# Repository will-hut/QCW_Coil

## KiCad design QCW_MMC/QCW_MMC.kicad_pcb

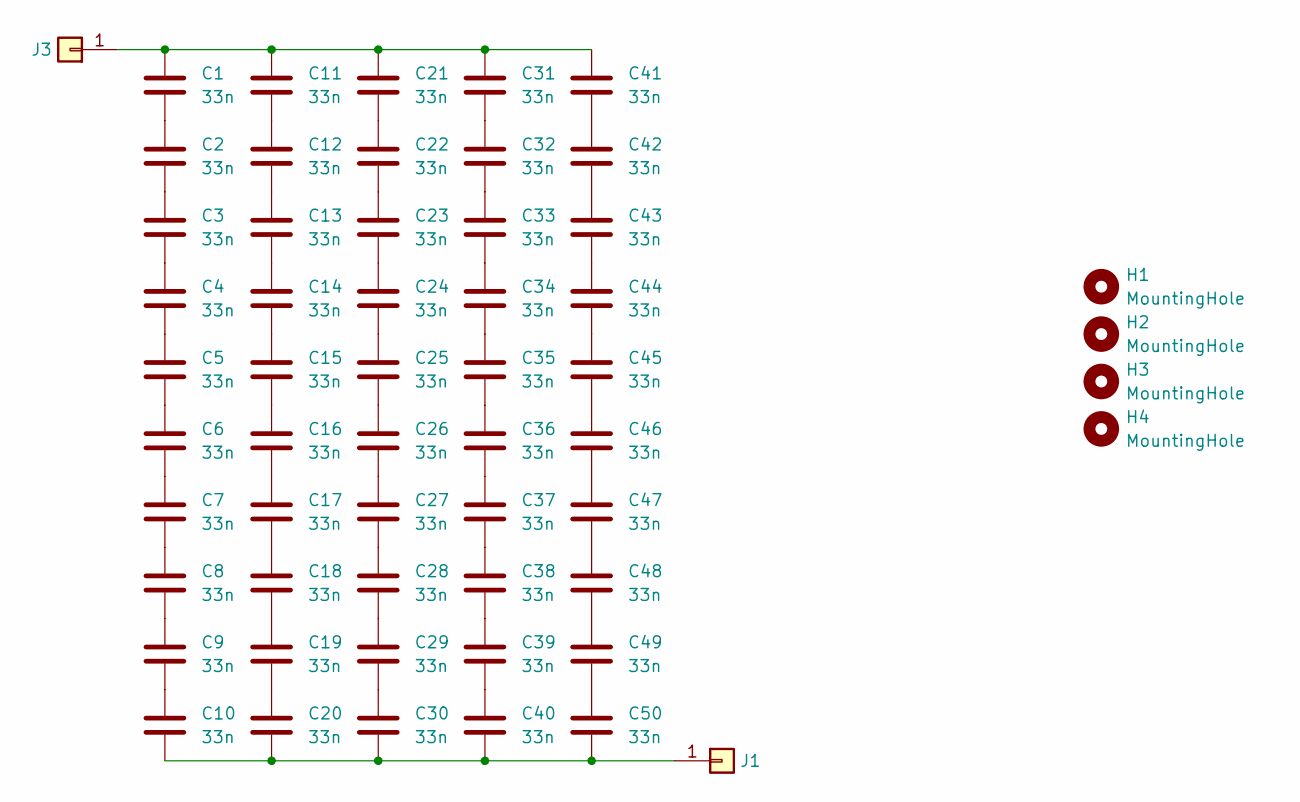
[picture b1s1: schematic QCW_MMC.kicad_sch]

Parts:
C1, C2, C3, C4, C5, C6, C7, C8, C9, C10, C11, C12, C13, C14, C15, C16, C17, C18, C19, C20, C21, C22, C23, C24, C25, C26, C27, C28, C29, C30, C31, C32, C33, C34, C35, C36, C37, C38, C39, C40, C41, C42, C43, C44, C45, C46, C47, C48, C49, C50: 33n; C_Rect_L18.0mm_W5.0mm_P15.00mm_FKS3_FKP3
H1, H2, H3, H4: MountingHole; MountingHole_5.3mm_M5
J1, J3: Conn_01x01; M6 Lug

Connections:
unnamed: C1.2, C2.1
unnamed: C2.2, C3.1
unnamed: C3.2, C4.1
unnamed: C4.2, C5.1
unnamed: C5.2, C6.1
unnamed: C6.2, C7.1
unnamed: C7.2, C8.1
unnamed: C8.2, C9.1
unnamed: C9.2, C10.1
unnamed: C11.2, C12.1
unnamed: C12.2, C13.1
unnamed: C13.2, C14.1
unnamed: C14.2, C15.1
unnamed: C15.2, C16.1
unnamed: C16.2, C17.1
unnamed: C17.2, C18.1
unnamed: C18.2, C19.1
unnamed: C19.2, C20.1
unnamed: C21.2, C22.1
unnamed: C22.2, C23.1
unnamed: C23.2, C24.1
unnamed: C24.2, C25.1
unnamed: C25.2, C26.1
unnamed: C26.2, C27.1
unnamed: C27.2, C28.1
unnamed: C28.2, C29.1
unnamed: C29.2, C30.1
unnamed: C31.2, C32.1
unnamed: C32.2, C33.1
unnamed: C33.2, C34.1
unnamed: C34.2, C35.1
unnamed: C35.2, C36.1
unnamed: C36.2, C37.1
unnamed: C37.2, C38.1
unnamed: C38.2, C39.1
unnamed: C39.2, C40.1
unnamed: C41.2, C42.1
unnamed: C42.2, C43.1
unnamed: C43.2, C44.1
unnamed: C44.2, C45.1
unnamed: C45.2, C46.1
unnamed: C46.2, C47.1
unnamed: C47.2, C48.1
unnamed: C48.2, C49.1
unnamed: C49.2, C50.1
unnamed: C10.2, C20.2, C30.2, C40.2, C50.2, J1.1
unnamed: C1.1, C11.1, C21.1, C31.1, C41.1, J3.1

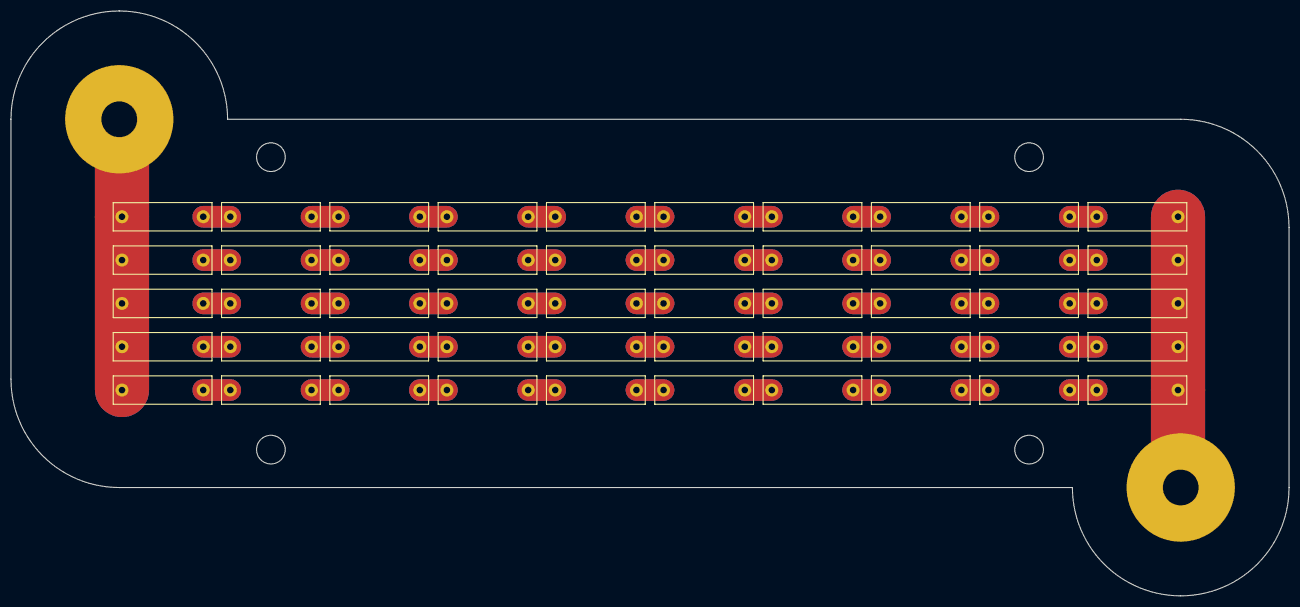
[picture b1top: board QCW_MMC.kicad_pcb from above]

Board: 2 copper layers, 236.0 x 108.0 mm, 56 parts (0 on the bottom side), 47 nets.

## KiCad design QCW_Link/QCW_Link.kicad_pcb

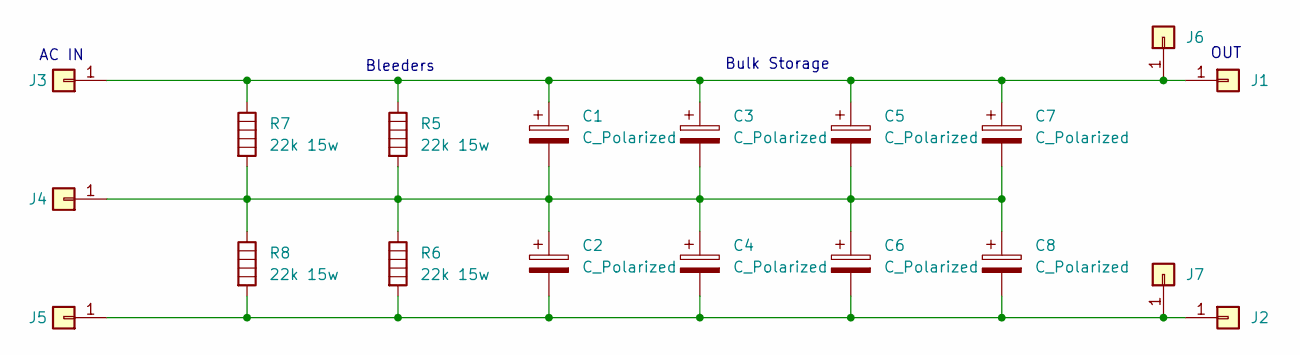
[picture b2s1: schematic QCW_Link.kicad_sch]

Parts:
C1, C2, C3, C4, C5, C6, C7, C8: C_Polarized; EPCOS B43456-S5129-M2
J1, J2, J3, J4, J5: Conn_01x01; M6 Lug
J6, J7: Conn_01x01; SolderWirePad_1x01_SMD_1.5x3mm
R5, R6, R7, R8: 22k 15w; R_Axial_Power_L48.0mm_W12.5mm_P55.88mm

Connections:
unnamed: C1.1, C3.1, C5.1, C7.1, J1.1, J3.1, J6.1, R5.1, R7.1
unnamed: C2.2, C4.2, C6.2, C8.2, J2.1, J5.1, J7.1, R6.2, R8.2
unnamed: C1.2, C2.1, C3.2, C4.1, C5.2, C6.1, C7.2, C8.1, J4.1, R5.2, R6.1, R7.2, R8.1

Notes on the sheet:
Bulk Storage
Bleeders
AC IN
OUT

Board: 2 copper layers, 19 parts (4 on the bottom side), 3 nets, no tracks yet.

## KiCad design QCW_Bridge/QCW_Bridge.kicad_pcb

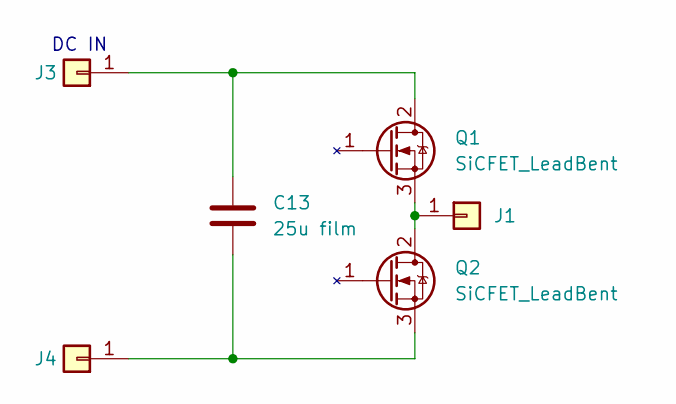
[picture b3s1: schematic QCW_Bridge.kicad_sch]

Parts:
C13: 25u film; EZPV1B256MTB
J1, J3, J4: Conn_01x01; WirePad_8AWG
Q1, Q2: SiCFET_LeadBent; PG-TO247 Bent

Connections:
unnamed: J1.1, Q1.3 (S), Q2.2 (D)
unnamed: C13.1, J3.1, Q1.2 (D)
unnamed: C13.2, J4.1, Q2.3 (S)

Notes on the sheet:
DC IN

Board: 2 copper layers, 6 parts (1 on the bottom side), 3 nets, no tracks yet.

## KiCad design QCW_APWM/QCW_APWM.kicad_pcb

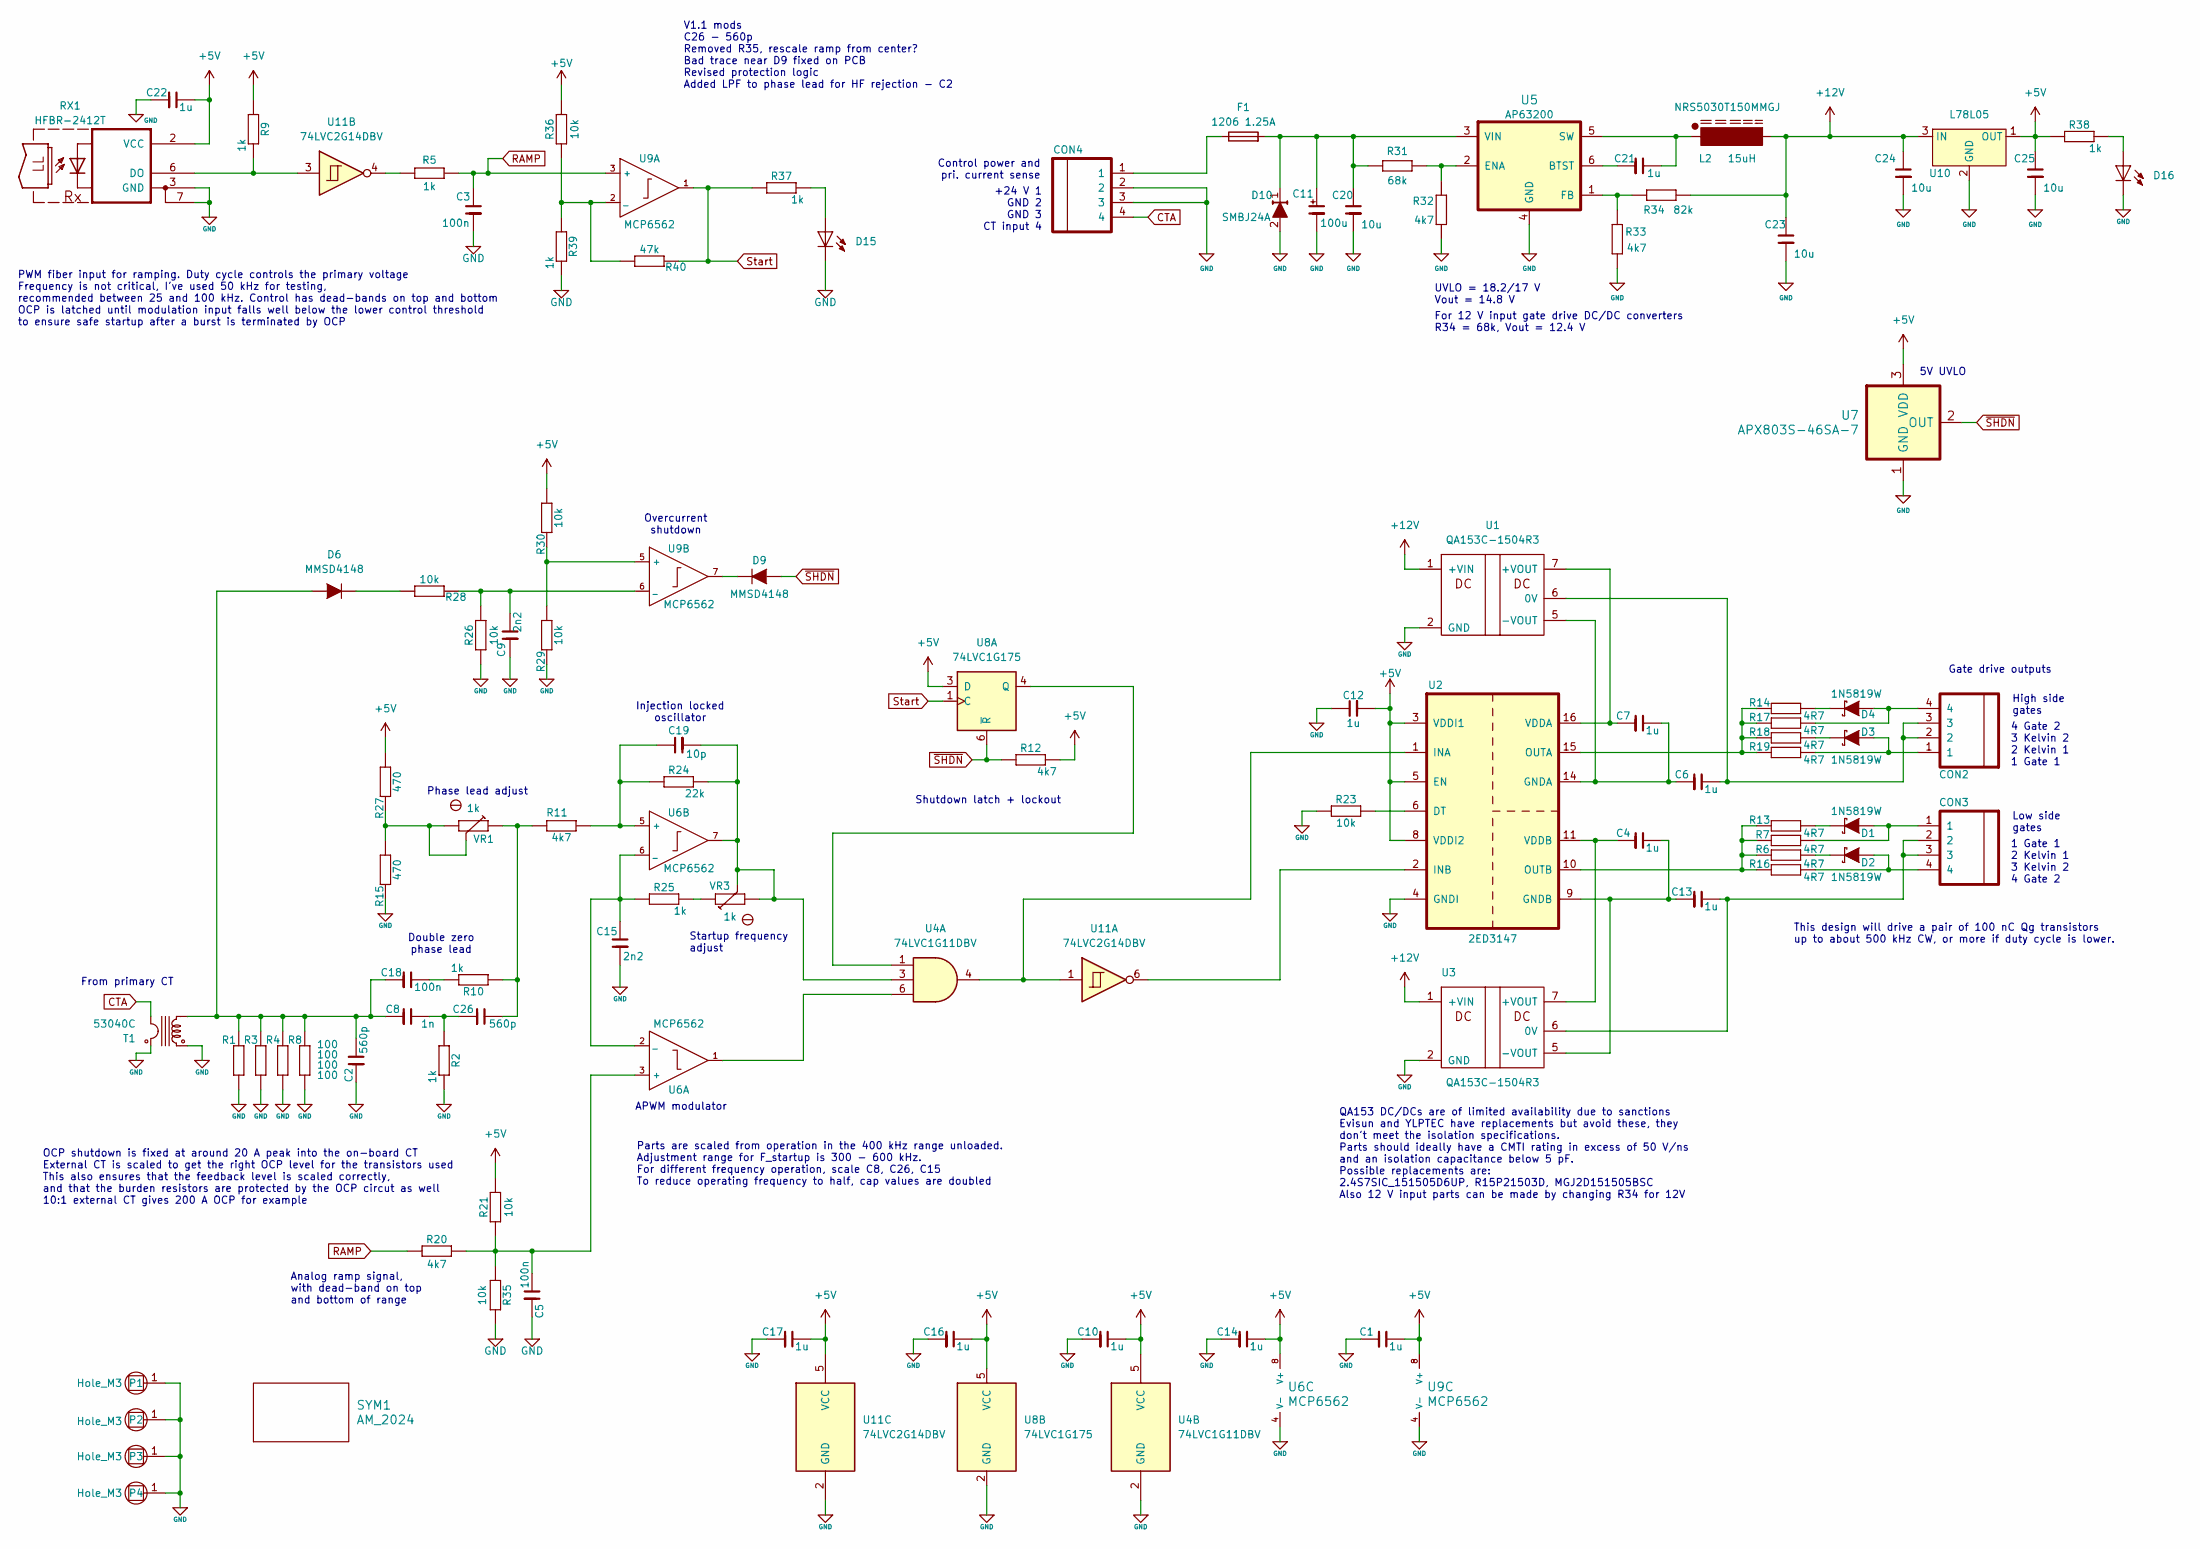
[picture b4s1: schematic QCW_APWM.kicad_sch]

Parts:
C1, C10, C12, C14, C16, C17, C21, C22: 1u; C_0805; Voltage 16V
C2: 560p; C_0805_2012Metric
C3, C5, C18: 100n; C_0805; Voltage 50V
C4, C6, C7, C13: 1u; C_0805; Voltage 35V
C8: 1n; C_0805
C9, C15: 2n2; C_0805; Voltage 50V
C11: 100u; c_elec_6.3x5.7; Voltage 50V
C19: 10p; C_0805
C20, C23, C24, C25: 10u; C_1206
C26: 560p; C_0805
CON2, CON3: Header_H_2x2; Pin_Header_Angled_2x02
CON4: Header_H_2x2; PhoenixContact_MC-G_04x3.50mm_Angled
D1, D2, D3, D4: 1N5819W; SOD-123
D6, D9: MMSD4148; SOD-123
D10: SMBJ24A; SMB_Standard
D15, D16: LED_3mm; LED_551-0807F
F1: 1206 1.25A; R_1206_hybrid
L2: NRS5030T150MMGJ; Choke_SMD_Taiyo_NRS50XX
P1, P2, P3, P4: Hole_M3; Hole_M3_plated
R1, R3, R4, R8: 100; R_1206; Tolerance 1%
R2, R5, R9, R10, R25, R37, R38, R39: 1k; R_0805_hybrid_2; Tolerance 1%
R6, R7, R13, R14, R16, R17, R18, R19: 4R7; R_1206; Tolerance 1%
R11, R12, R20, R32, R33: 4k7; R_0805_hybrid_2; Tolerance 1%
R15, R27: 470; R_0805_hybrid_2; Tolerance 1%
R21, R23, R26, R28, R29, R30, R35, R36: 10k; R_0805_hybrid_2; Tolerance 1%
R24: 22k; R_0805_hybrid_2; Tolerance 1%
R31: 68k; R_0805_hybrid_2; Tolerance 1%
R34: 82k; C_0603_1608Metric; Tolerance 1%
R40: 47k; R_0805_hybrid_2; Tolerance 1%
RX1: HFBR-2412T; HFBR-X41XT
SYM1: AM_2024; am24_22mm
T1: 53040C; Murata_5300
U1, U3: QA153C-1504R3
U2: 2ED3147; SOIC-14of16_3.9x9.9mm_Pitch1.27mm_wide_narrow
U4: 74LVC1G11DBV; SOT-23-6
U5: AP63200; SOT-23-6
U6, U9: MCP6562; SOIC-8_3.9x4.9mm_Pitch1.27mm
U7: APX803S-46SA-7; SOT-23
U8: 74LVC1G175; SOT-23-6
U10: L78L05; SOT89-3_Housing
U11: 74LVC2G14DBV; SOT-23-6
VR1, VR3: 1k; Potentiometer_Bourns_3296Z_3-8Zoll_Angular_ScrewFront; Tolerance 10%

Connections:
+5V: C1.2 (K), C10.2 (K), C12.1 (A), C14.2 (K), C16.2 (K), C17.2 (K), C22.2 (K), C25.2 (K), R9.1, R12.2, R21.1, R27.1, R30.1, R36.2, R38.1, RX1.2 (VCC), U2.3 (VDDI1), U2.5 (EN), U2.8 (VDDI2), U4.5 (VCC), U6.8 (V+), U7.3 (VDD), U8.3 (D), U8.5 (VCC), U9.8 (V+), U10.1 (OUT), U11.5 (VCC)
+12V: C23.2 (K), C24.2 (K), L2.1, R34.2, U1.1 (+VIN), U3.1 (+VIN), U10.3 (IN)
CTA: CON4.4, T1.7 (P2)
GND: C1.1 (A), C2.1 (A), C3.1 (A), C5.1 (A), C9.1 (A), C10.1 (A), C11.2 (K), C12.2 (K), C14.1 (A), C15.1 (A), C16.1 (A), C17.1 (A), C20.1 (A), C22.1 (A), C23.1 (A), C24.1 (A), C25.1 (A), CON4.2, CON4.3, D10.2, D15.C, D16.C, P1.1, P2.1, P3.1, P4.1, R1.1, R2.2, R3.1, R4.1, R8.1, R15.2, R23.2, R26.1, R29.2, R32.1, R33.1, R35.1, R39.2, RX1.3 (GND), RX1.7, T1.1 (S1), T1.8 (P1), U1.2 (GND), U2.4 (GNDI), U3.2 (GND), U4.2 (GND), U5.4 (GND), U6.4 (V-), U7.1 (GND), U8.2 (GND), U9.4 (V-), U10.2 (GND), U11.2 (GND)
unnamed: C4.1 (A), U2.11 (VDDB), U3.7 (+VOUT)
unnamed: C5.2 (K), R20.1, R21.2, R35.2, U6.3 (+)
unnamed: C6.1 (A), C7.2 (K), U1.5 (-VOUT), U2.14 (GNDA)
unnamed: C6.2 (K), CON2.2, CON2.3, U1.6 (0V)
unnamed: C7.1 (A), U1.7 (+VOUT), U2.16 (VDDA)
unnamed: C9.2 (K), R26.2, R28.2, U9.6 (_)
unnamed: C11.1 (A), C20.2 (K), D10.1, F1.2, R31.2, U5.3 (VIN)
unnamed: C4.2 (K), C13.1 (A), U2.9 (GNDB), U3.5 (-VOUT)
unnamed: C13.2 (K), CON3.2, CON3.3, U3.6 (0V)
unnamed: C15.2 (K), R25.1, U6.2 (_), U6.6 (_)
unnamed: C2.2 (K), C8.1 (A), C18.1 (A), D6.2 (A), R1.2, R3.2, R4.2, R8.2, T1.3 (S2)
unnamed: C18.2 (K), R10.2
unnamed: C19.1 (A), R24.2, U4.3, U6.7, VR3.2, VR3.3
unnamed: C19.2 (K), R11.2, R24.1, U6.5 (+)
unnamed: C21.1 (A), U5.6 (BTST)
unnamed: C21.2 (K), L2.2, U5.5 (SW)
unnamed: C8.2 (K), C26.1 (A), R2.1
unnamed: C26.2 (K), R10.1, R11.1, VR1.1
unnamed: CON4.1, F1.1
unnamed: CON3.1, D1.2 (A), R7.2
unnamed: D1.1 (K), R13.2
unnamed: CON3.4, D2.2 (A), R16.2
unnamed: D2.1 (K), R6.2
unnamed: CON2.1, D3.2 (A), R19.2
unnamed: D3.1 (K), R18.2
unnamed: CON2.4, D4.2 (A), R17.2
unnamed: D4.1 (K), R14.2
unnamed: D6.1 (K), R28.1
unnamed: D9.1 (K), U9.7
unnamed: D15.A, R37.2
unnamed: D16.A, R38.2
unnamed: R5.2, U11.4
unnamed: R15.1, R27.2, VR1.2, VR1.3
unnamed: R25.2, VR3.1
unnamed: R9.2, RX1.6 (DO), U11.3
unnamed: R23.1, U2.6 (DT)
unnamed: U2.1 (INA), U4.4, U11.1
unnamed: U2.2 (INB), U11.6
unnamed: R14.1, R17.1, R18.1, R19.1, U2.15 (OUTA)
unnamed: R6.1, R7.1, R13.1, R16.1, U2.10 (OUTB)
unnamed: U4.6, U6.1
unnamed: R31.1, R32.2, U5.2 (ENA)
unnamed: R33.2, R34.1, U5.1 (FB)
unnamed: U4.1, U8.4 (Q)
unnamed: R36.1, R39.1, R40.1, U9.2 (_)
unnamed: R29.1, R30.2, U9.5 (+)
RAMP: C3.2 (K), R5.1, R20.2, U9.3 (+)
Start: R37.1, R40.2, U8.1 (C), U9.1
~SHDN: D9.2 (A), R12.1, U7.2 (OUT), U8.6 (~R)

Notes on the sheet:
From primary CT
High side gates
V1.1 mods C26 - 560p Removed R35, rescale ramp from center? Bad trace near D9 fixed on PCB Revised protection logic Added LPF to phase lead for HF rejection - C2
Phase lead adjust
QA153 DC/DCs are of limited availability due to sanctions Evisun and YLPTEC have replacements but avoid these, they don't meet the isolation specifications. Parts should ideally have a CMTI rating in excess of 50 V/ns and an isolation capacitance below 5 pF. Possible replacements are: 2.4S7SIC_1515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
Startup frequency adjust
APWM modulator
This design will drive a pair of 100 nC Qg transistors up to about 500 kHz CW, or more if duty cycle is lower.
Overcurrent shutdown
Gate drive outputs
Low side gates
Control power and pri. current sense
4 Gate 2 3 Kelvin 2 2 Kelvin 1 1 Gate 1
Shutdown latch + lockout
1 Gate 1 2 Kelvin 1 3 Kelvin 2 4 Gate 2
Parts are scaled from operation in the 400 kHz range unloaded. Adjustment range for F_startup is 300 - 600 kHz. For different frequency operation, scale C8, C26, C15 To reduce operating frequency to half, cap values are doubled
PWM fiber input for ramping. Duty cycle controls the primary voltage Frequency is not critical, I've used 50 kHz for testing, recommended between 25 and 100 kHz. Control has dead-bands on top and bottom OCP is latched until modulation input falls well below the lower control threshold to ensure saf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
5V UVLO
Analog ramp signal, with dead-band on top and bottom of range
Double zero phase lead
UVLO = 18.2/17 V Vout = 14.8 V
OCP shutdown is fixed at around 20 A peak into the on-board CT External CT is scaled to get the right OCP level for the transistors used This also ensures that the feedback level is scaled correctly, and that the burden resistors are protected by the OCP circut as well 10:1 external CT gives 200 A 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
+24 V 1 GND 2 GND 3 CT input 4
For 12 V input gate drive DC/DC converters R34 = 68k, Vout = 12.4 V
Injection locked oscillator

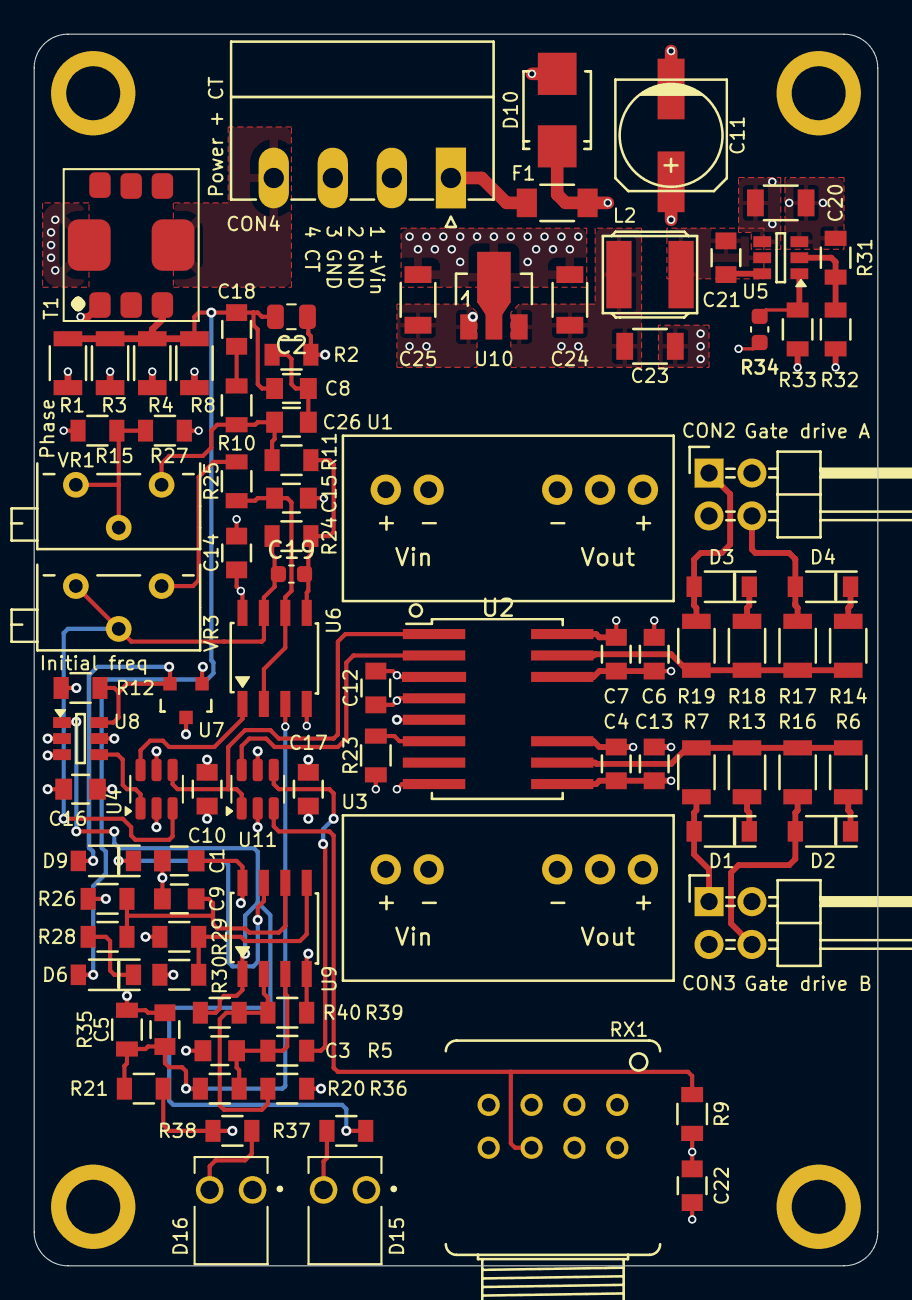
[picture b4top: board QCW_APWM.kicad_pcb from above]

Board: 4 copper layers, 50.0 x 73.0 mm, 99 parts (1 on the bottom side), 53 nets.

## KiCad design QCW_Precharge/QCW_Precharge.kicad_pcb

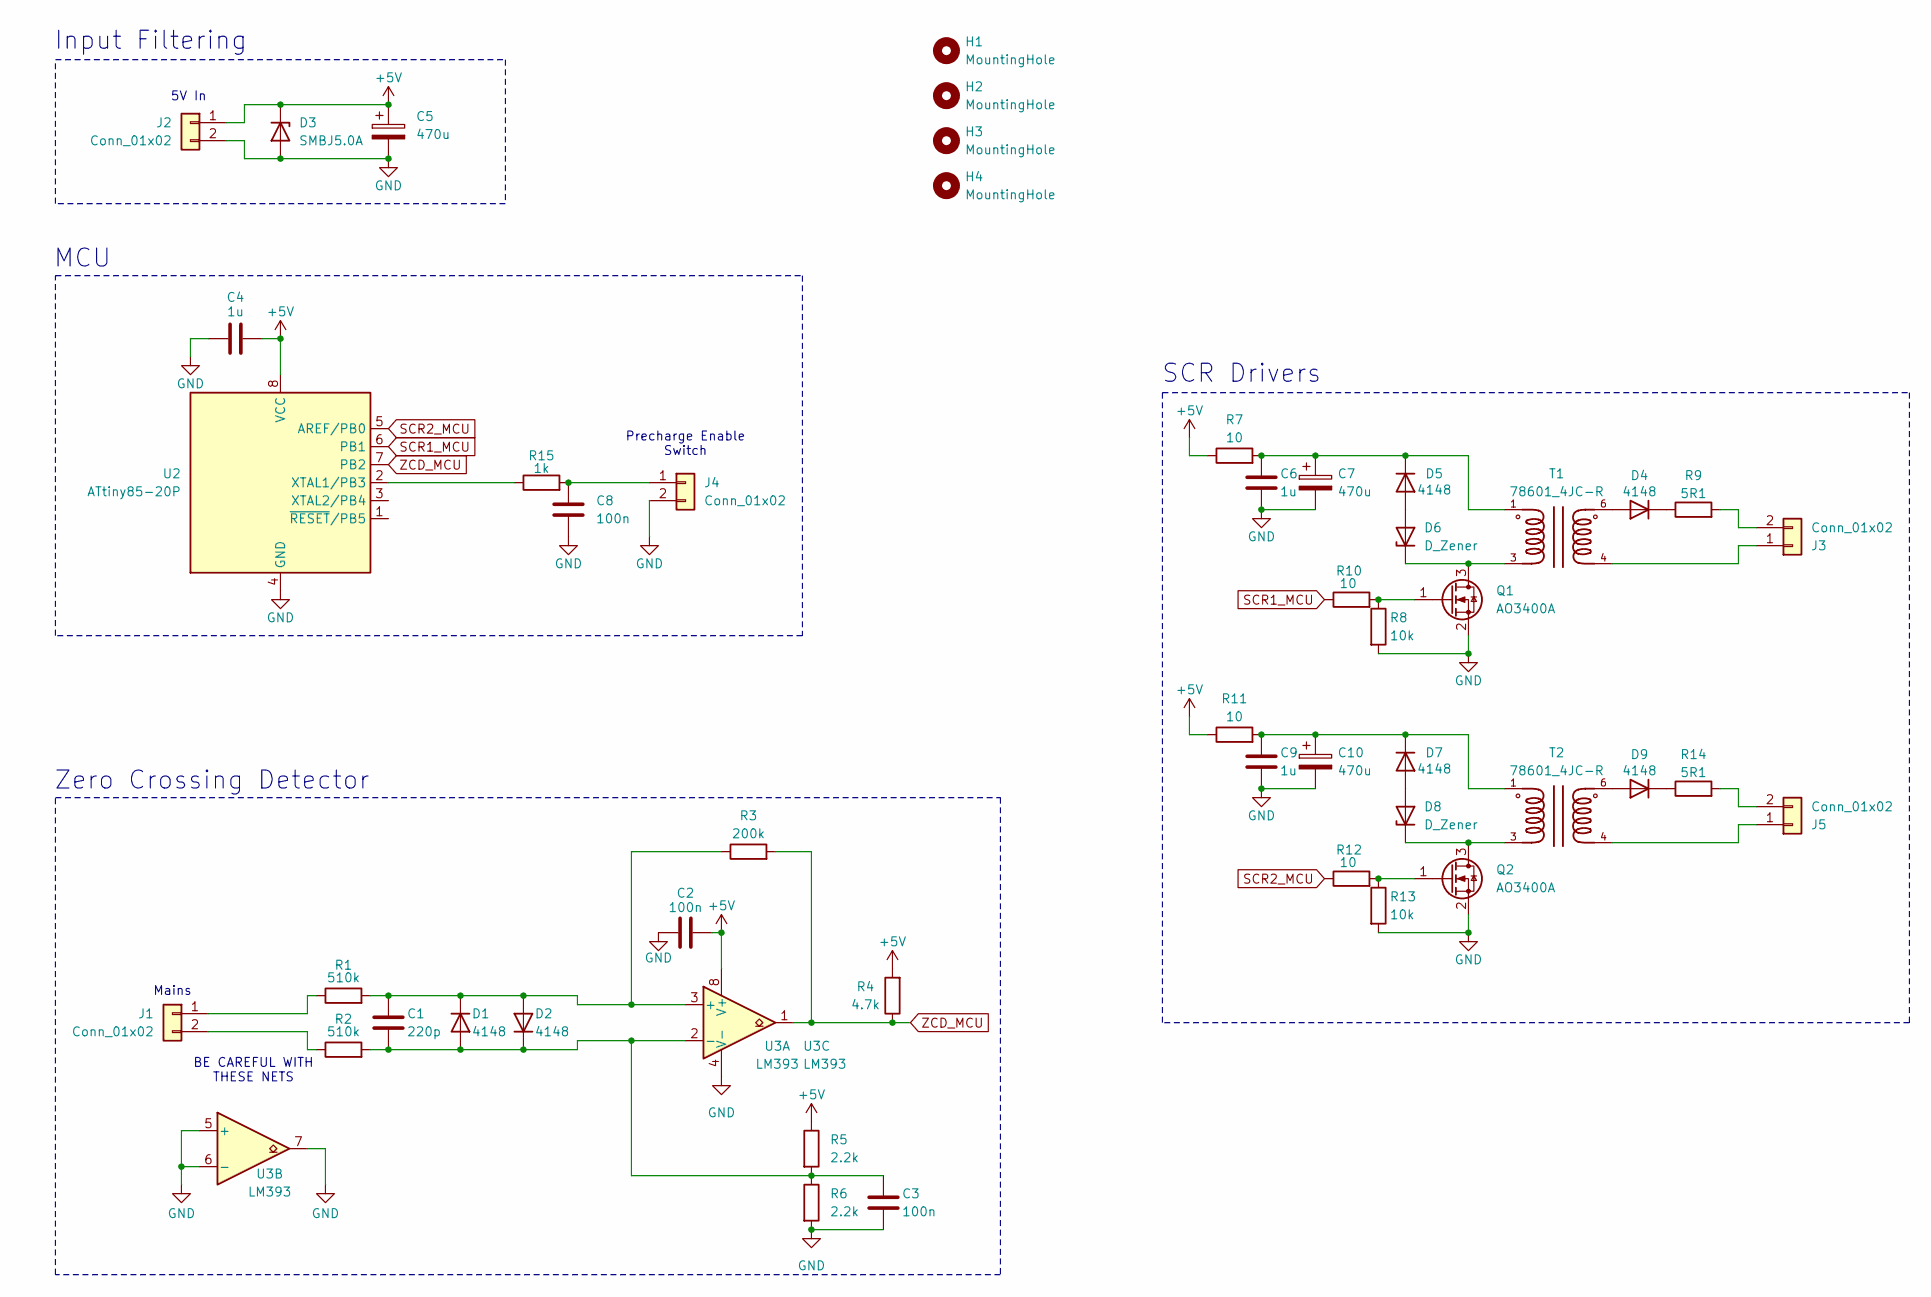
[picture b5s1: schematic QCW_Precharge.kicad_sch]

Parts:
C1: 220p; C_0603_1608Metric; LCSC C1603
C2, C3, C8: 100n; C_0603_1608Metric; LCSC C14663
C4, C6, C9: 1u; C_0603_1608Metric; LCSC C15849
C5, C7, C10: 470u; CP_Radial_D10.0mm_P5.00mm
D1, D2, D4, D5, D7, D9: 4148; D_SOD-123; LCSC C81598
D3: SMBJ5.0A; D_SMB
D6, D8: D_Zener; D_SMA
H1, H2, H3, H4: MountingHole; MountingHole_3.2mm_M3
J1, J2, J3, J4, J5: Conn_01x02; TerminalBlock_Phoenix_MKDS-1,5-2-5.08_1x02_P5.08mm_Horizont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
Q1, Q2: AO3400A; SOT-23; LCSC C20917
R1, R2: 510k; R_1206_3216Metric; LCSC C23192
R3: 200k; R_0603_1608Metric; LCSC C25811
R4: 4.7k; R_0603_1608Metric; LCSC C23162
R5, R6: 2.2k; R_0603_1608Metric; LCSC C4190
R7, R11: 10; R_2010_5025Metric
R8, R13: 10k; R_0603_1608Metric; LCSC C25804
R9, R14: 5R1; R_2010_5025Metric
R10, R12: 10; R_0603_1608Metric; LCSC C22859
R15: 1k; R_0603_1608Metric; LCSC C21190
T1, T2: 78601_4JC-R; XFMR_78601_4JC-R
U2: ATtiny85-20P; DIP-8_W7.62mm
U3: LM393; SOIC-8_3.9x4.9mm_P1.27mm; LCSC C7955

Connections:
+5V: C2.2, C4.2, C5.1, D3.1 (K), J2.1, R4.2, R5.1, R7.1, R11.1, U2.8 (VCC), U3.8 (V+)
GND: C2.1, C3.2, C4.1, C5.2, C6.2, C7.2, C8.2, C9.2, C10.2, D3.2 (A), J2.2, J4.2, Q1.2 (S), Q2.2 (S), R6.2, R8.2, R13.2, U2.4 (GND), U3.4 (V-), U3.5 (+), U3.6 (-), U3.7
unnamed: C1.2, C3.1, D1.2 (A), D2.1 (K), R2.2, R5.2, R6.1, U3.2 (-)
unnamed: C1.1, D1.1 (K), D2.2 (A), R1.2, R3.1, U3.3 (+)
unnamed: D4.2 (A), T1.6
unnamed: D4.1 (K), R9.1
unnamed: D5.2 (A), D6.2 (A)
unnamed: C6.1, C7.1, D5.1 (K), R7.2, T1.1
unnamed: D6.1 (K), Q1.3 (D), T1.3
unnamed: D7.2 (A), D8.2 (A)
unnamed: C9.1, C10.1, D7.1 (K), R11.2, T2.1
unnamed: D8.1 (K), Q2.3 (D), T2.3
unnamed: D9.2 (A), T2.6
unnamed: D9.1 (K), R14.1
unnamed: J1.1, R1.1
unnamed: J1.2, R2.1
unnamed: J3.1, T1.4
unnamed: J3.2, R9.2
unnamed: C8.1, J4.1, R15.2
unnamed: J5.1, T2.4
unnamed: J5.2, R14.2
unnamed: Q1.1 (G), R8.1, R10.2
unnamed: Q2.1 (G), R12.2, R13.1
unnamed: R15.1, U2.2 (XTAL1/PB3)
SCR1_MCU: R10.1, U2.6 (PB1)
SCR2_MCU: R12.1, U2.5 (AREF/PB0)
ZCD_MCU: R3.2, R4.1, U2.7 (PB2), U3.1

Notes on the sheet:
Input Filtering
MCU
SCR Drivers
5V In
Mains
Zero Crossing Detector
BE CAREFUL WITH THESE NETS
Precharge Enable Switch

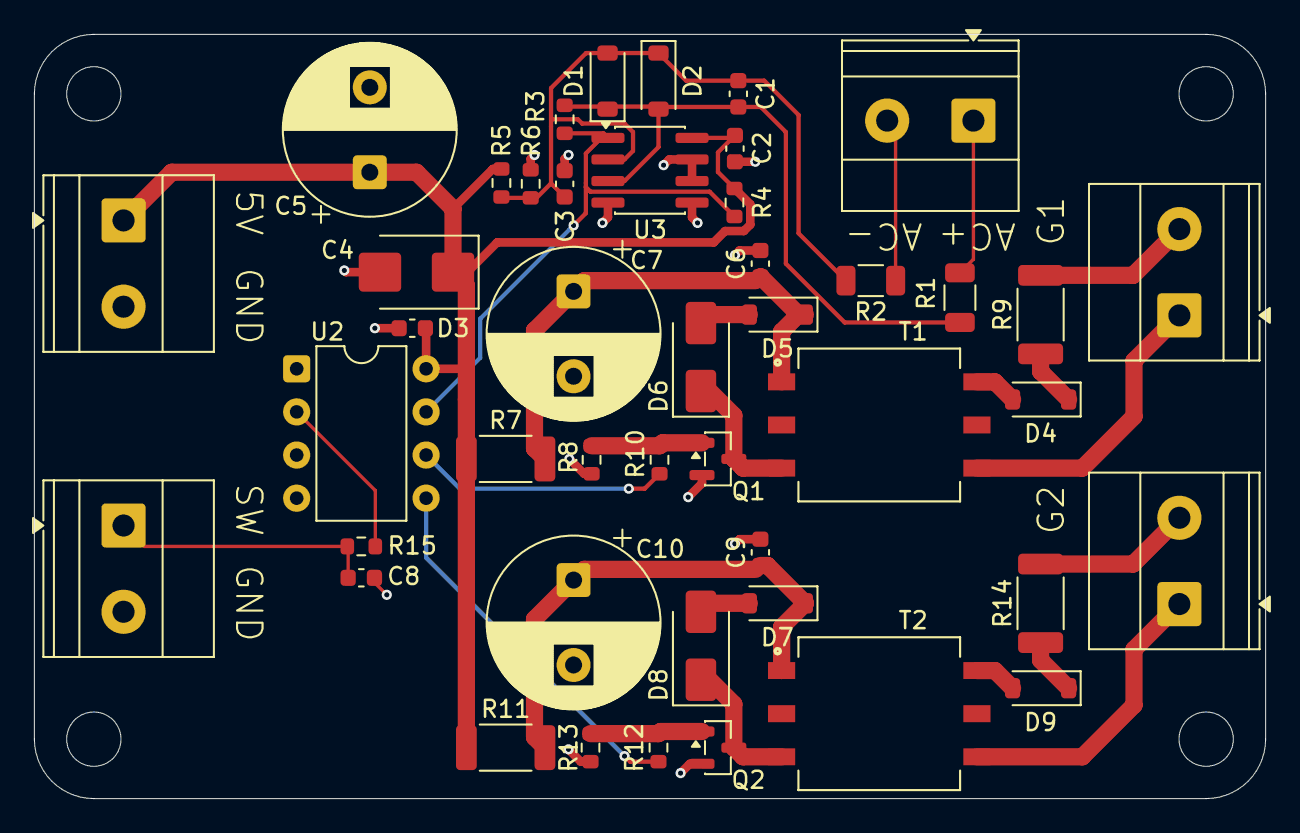
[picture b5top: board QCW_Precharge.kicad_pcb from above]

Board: 2 copper layers, 72.5 x 45.0 mm, 49 parts (0 on the bottom side), 27 nets.

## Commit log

2025-12-23 Pushed all PCBs & JavaTC file
2026-01-05 update bridge
2026-01-14 Adjust JavaTC coil dimensions to match model
